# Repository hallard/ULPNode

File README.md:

ULPNode
=======

Utra Low Power Wireless Arduino Node

For some time being, I researching a way to have to have a kind of “universal” Arduino node sensor.  
When I say universal, I’m talking about connecting to it several sensors like Temperature, Humidity, Lux,… such as LDR, NTC, PTC, DHT11, DHT22, DS18B20, I2C sensors.  

At 1st research I tried lot existing, they  works fine, but as soon as you want to power them with classic battery (one AAA, CR2032, …) you’re facing other challenges, be able to maximize the battery life and also be able to send wireless frames until battery is reaching it’s end of life.

##Blog dedicated post
See this [post][2] for detailed and technical information

##License

Copyright Charles-Henri Hallard (2014)  
[Attribution-ShareAlike CC BY-SA][6]

##Misc
Do not hesitate to look on news and other projects on my [blog][1] 
 
[1]: http://hallard.me
[2]: http://hallard.me/bp-ulpnode/
[3]: http://hallard.me/ulpnode-bootloader/
[6]: https://creativecommons.org/licenses/

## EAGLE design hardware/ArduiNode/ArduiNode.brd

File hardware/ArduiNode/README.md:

Arduinode V1.3
==============

Very first early prototype of Utra Low Power Wireless Arduino Node. In fact it's amazing how often I use this board for testing, it runs on 3.3V, has RFM12B RFM69 connector, NRF24 style connector, I2C Oled connector and some sensors connectors.

It does not include the [Low Power][5] engine of ULPNode but it's a really cool testing board.

**This is not the final design**, this board was done to implement 1st testing and POC, it's posted there as reference only and as help on some Arduino Sketch I wrote that I use with this board. It also include 2 little battery power testing board with different version of MCP1640 DC/DC booster.

##Blog dedicated categories
See this [post][4] for detailed and technical information on ULPNode

##License

Copyright Charles-Henri Hallard (2014)  
[Attribution-ShareAlike CC BY-SA][6]

##Misc
Do not hesitate to look on news and other projects on my [blog][1] 

##schematics

Do not hesitate to look on news and other projects on my [blog][1] 
 
[1]: http://hallard.me
[2]: http://hallard.me/bp-ulpnode/
[3]: http://hallard.me/ulpnode-bootloader/
[4]: http://hallard.me/category/ulpnode/
[5]: http://hallard.me/ulpnode-low-power-secret/
[6]: https://creativecommons.org/licenses/

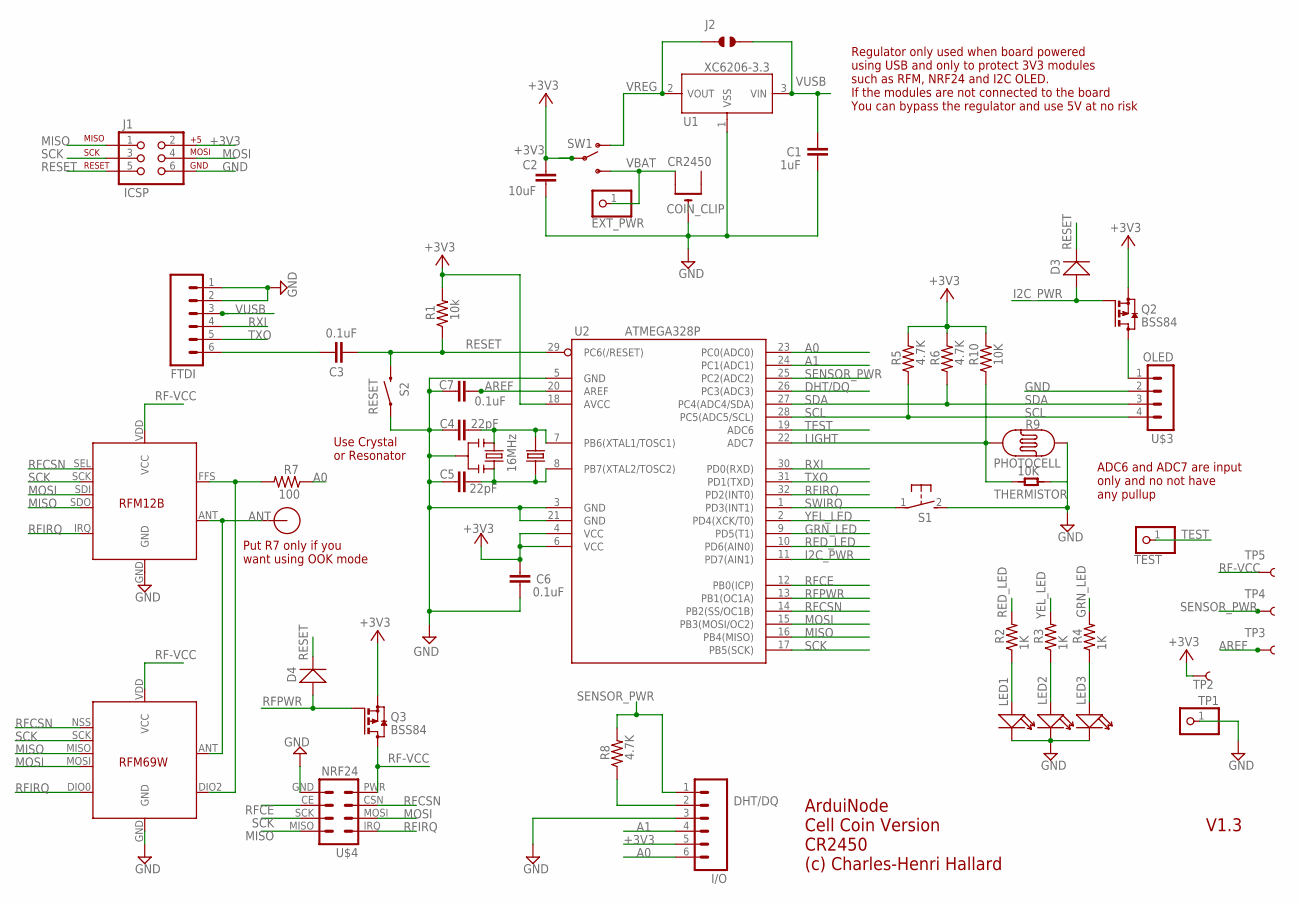
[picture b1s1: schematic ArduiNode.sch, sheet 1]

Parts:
C1: 1uF; C0805K
C2: 10uF; C0805K
C3, C6, C7: 0.1uF; C0805K
C4, C5: 22pF; C0805K
COIN_CLIP: CR2450; CR1220-THM
D3, D4: D-SOD-123; SOD123
EXT_PWR: PINHD-1X1CB; 1X01-CLEANBIG
FTDI: M06SIP_LOCK; 1X06-SIP_LOCK
I/O: M06FEMALE_LOCK; 1X06_FEMALE_LOCK.010
J1: ICSP; 2X3_LOCK
J2: JUMPER_SOLDER_1X2
LED1, LED2, LED3: LED0805; LED-0805
Q2, Q3: BSS84; SOT23
R1: 10k; M0805
R2, R3, R4: 1K; M0805
R5, R6, R8: 4.7K; M0805
R7: 100; M0805
R9: PHOTOCELL
R10: 10K; M0805
RFM12B: RFM12BNO; RFM12B
S1: DTS-3
S2: RESET; TACTILE-SWITCH-1101NE
SW1: USB_COIN; SWITCH-SPDT-SMD
TEST: PINHD-1X1CB; 1X01-CLEANBIG
THERMISTOR: 10K; R0603
TP1: PINHD-1X1; 1X01
TP2, TP3, TP4, TP5: TEST-POINT3X5; PAD.03X.05
U1: XC6206-3.3; SOT23
U2: ATMEGA328P; TQFP32
U$3: OLED; 1X04_LOCK
U$4: NRF24; 2X04_LOCK
U$11: RFM12B_ANTENNA; RFM12B-ANTENNA
X2: 16MHz; 2P-SMD-5.0X3.2
X3: RFM69; RFM69W-MINPADS
Y1: 16MHz; RESONATOR-SMD

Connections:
+3V3: C2.1, C6.2, I/O.5, J1.2, Q2.2 (S), Q3.2 (S), R1.2, R5.2, R6.2, R10.2, SW1.2, TP2.P$1, U2.4 (VCC), U2.6 (VCC), U2.18 (AVCC)
A0: I/O.6, R7.1, U2.23 (PC0(ADC0))
A1: I/O.4, U2.24 (PC1(ADC1))
ANT: RFM12B.ANT, U$11.P$1, X3.ANT
AREF: C7.1, TP3.P$1, U2.20 (AREF)
DHT/DQ: I/O.2, R8.1, U2.26 (PC3(ADC3))
DTR: C3.1, FTDI.6
GND: C1.2, C2.2, C4.2, C5.2, C6.1, C7.2, COIN_CLIP.GND (-), FTDI.1, FTDI.2, I/O.3, J1.6, LED1.-, LED2.-, LED3.-, R9.1, RFM12B.GND, S1.2, S2.P$1 (1), THERMISTOR.1, TP1.1, U1.1 (VSS), U2.3 (GND), U2.5 (GND), U2.21 (GND), U$3.2, U$4.GND, X3.GND, Y1.2
GRN_LED: R4.2, U2.9 (PD5(T1))
I2C_PWR: D3.+, Q2.1 (G), U2.11 (PD7(AIN1))
LIGHT: R9.2, R10.1, THERMISTOR.2, U2.22 (ADC7)
MISO: J1.1, RFM12B.SDO, U2.16 (PB4(MISO)), U$4.MISO, X3.MISO
MOSI: J1.4, RFM12B.SDI, U2.15 (PB3(MOSI/OC2)), U$4.MOSI, X3.MOSI
unnamed: R7.2, RFM12B.FFS, X3.DIO2
unnamed: LED1.+, R2.1
unnamed: LED2.+, R3.1
unnamed: LED3.+, R4.1
unnamed: Q2.3 (D), U$3.1
RED_LED: R2.2, U2.10 (PD6(AIN0))
RESET: C3.2, D3.-, D4.-, J1.5, R1.1, S2.P$2 (2), U2.29 (PC6(/RESET))
RF-VCC: Q3.3 (D), RFM12B.VDD (VCC), TP5.P$1, U$4.PWR (VCC), X3.VDD (VCC)
RFCE: U2.12 (PB0(ICP)), U$4.CE
RFCSN: RFM12B.SEL, U2.14 (PB2(SS/OC1B)), U$4.CSN, X3.NSS (SEL)
RFIRQ: RFM12B.IRQ, U2.32 (PD2(INT0)), U$4.IRQ, X3.DIO0
RFPWR: D4.+, Q3.1 (G), U2.13 (PB1(OC1A))
RXI: FTDI.4, U2.30 (PD0(RXD))
SCK: J1.3, RFM12B.SCK, U2.17 (PB5(SCK)), U$4.SCK (CLK), X3.SCK
SCL: R5.1, U2.28 (PC5(ADC5/SCL)), U$3.4
SDA: R6.1, U2.27 (PC4(ADC4/SDA)), U$3.3
SENSOR_PWR: I/O.1, R8.2, TP4.P$1, U2.25 (PC2(ADC2))
SWIRQ: S1.1, U2.1 (PD3(INT1))
TEST: TEST.1, U2.19 (ADC6)
TXO: FTDI.5, U2.31 (PD1(TXD))
VBAT: COIN_CLIP.+1 (+), EXT_PWR.1, SW1.1
VREG: J2.1, SW1.3, U1.2 (VOUT)
VUSB: C1.1, FTDI.3, J2.2, U1.3 (VIN)
X1: C5.1, U2.8 (PB7(XTAL2/TOSC2)), X2.1, Y1.3
XTAL1: C4.1, U2.7 (PB6(XTAL1/TOSC1)), X2.2, Y1.1
YEL_LED: R3.2, U2.2 (PD4(XCK/T0))

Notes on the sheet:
V1.3
ArduiNode Cell Coin Version CR2450 (c) Charles-Henri Hallard
Put R7 only if you want using OOK mode
Regulator only used when board powered using USB and only to protect 3V3 modules such as RFM, NRF24 and I2C OLED. If the modules are not connected to the board You can bypass the regulator and use 5V at no risk
ADC6 and ADC7 are input only and no not have any pullup
Use Crystal or Resonator

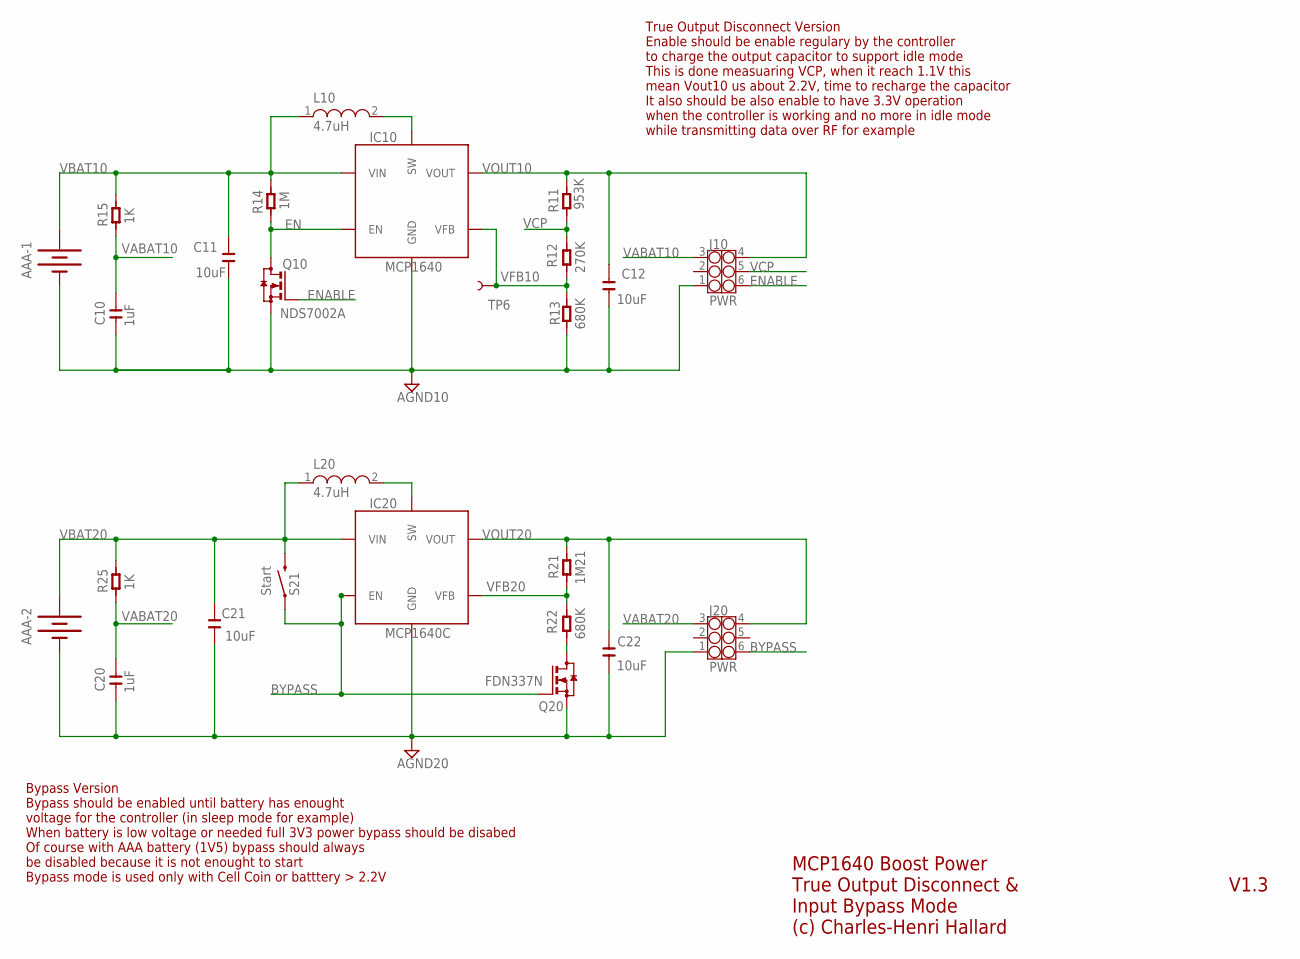
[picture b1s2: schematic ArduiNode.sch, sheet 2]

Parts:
AAA-1, AAA-2: BATTERYAAA-JL; BATTERY-AAA-JL
C10, C20: 1uF; C0805
C11, C12, C21, C22: 10uF; C0805
IC10: MCP1640; SOT23-6
IC20: MCP1640C; SOT23-6
J10, J20: PWR; 2X3P-2.54-2.54-11.6-3.0-BLACK-MALE
L10, L20: 4.7uH; L1812
Q10: NDS7002A; SOT23
Q20: FDN337N; SOT23
R11: 953K; R0603
R12: 270K; R0603
R13, R22: 680K; R0603
R14: 1M; R0603
R15, R25: 1K; R0603
R21: 1M21; R0603
S21: Start; TACTILE-SWITCH-1101NE
TP6: TEST-POINT3; PAD.03X.03

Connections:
AGND10: AAA-1.GND@1 (-), C10.1, C11.1, C12.1, IC10.2 (GND), J10.1, Q10.2 (S), R13.1
AGND20: AAA-2.GND@1 (-), C20.1, C21.1, C22.1, IC20.2 (GND), J20.1, Q20.2 (S)
BYPASS: IC20.3 (EN), J20.6, Q20.1 (G), S21.P$1 (1)
EN: IC10.3 (EN), Q10.3 (D), R14.1
ENABLE: J10.6, Q10.1 (G)
unnamed: Q20.3 (D), R22.1
SW: IC10.1 (SW), L10.2
SW20: IC20.1 (SW), L20.2
VABAT10: C10.2, J10.3, R15.1
VABAT20: C20.2, J20.3, R25.1
VBAT10: AAA-1.PWR@1 (+), C11.2, IC10.6 (VIN), L10.1, R14.2, R15.2
VBAT20: AAA-2.PWR@1 (+), C21.2, IC20.6 (VIN), L20.1, R25.2, S21.P$2 (2)
VCP: J10.5, R11.1, R12.2
VFB10: IC10.4 (VFB), R12.1, R13.2, TP6.P$1
VFB20: IC20.4 (VFB), R21.1, R22.2
VOUT10: C12.2, IC10.5 (VOUT), J10.4, R11.2
VOUT20: C22.2, IC20.5 (VOUT), J20.4, R21.2

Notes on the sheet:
MCP1640 Boost Power True Output Disconnect & Input Bypass Mode (c) Charles-Henri Hallard
True Output Disconnect Version Enable should be enable regulary by the controller to charge the output capacitor to support idle mode This is done measuaring VCP, when it reach 1.1V this mean Vout10 us about 2.2V, time to recharge the capacitor It also should be also enable to have 3.3V operation w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
Bypass Version Bypass should be enabled until battery has enought voltage for the controller (in sleep mode for example) When battery is low voltage or needed full 3V3 power bypass should be disabed Of course with AAA battery (1V5) bypass should always be disabled because it is not enought to start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
V1.3

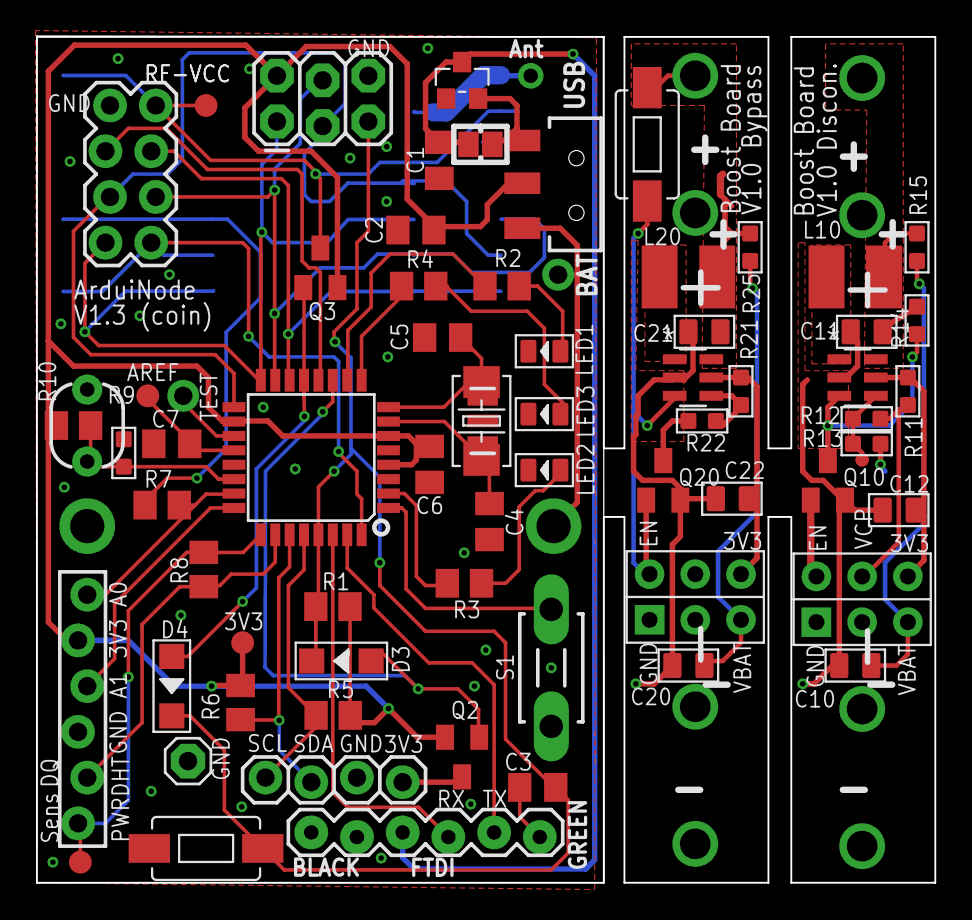
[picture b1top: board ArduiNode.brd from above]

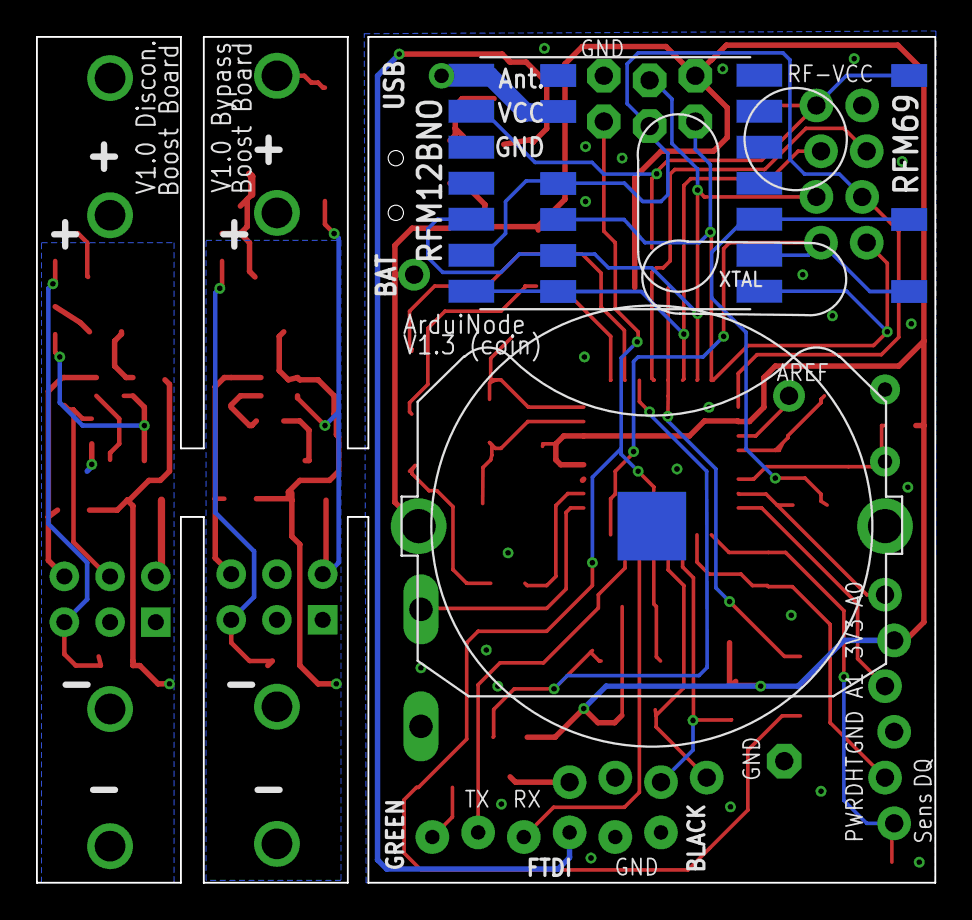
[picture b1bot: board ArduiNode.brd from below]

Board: 2 copper layers, 49.9 x 47.0 mm, 75 parts (3 on the bottom side), 56 nets.

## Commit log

2014-09-21 :confetti_ball: Added .gitattributes & .gitignore files
2014-09-21 Original Optiboot V6.2
    Cloned from google code trunk
2014-09-21 Presentation
2014-09-24 Modified for ULPNode
    First commit, modified for ULPNode, added sample sketch to call
    bootloader function
2014-09-24 Installation path typo error
2014-09-24 Added some comments
2014-09-24 Changed look & feel
2015-01-14 Updated speed to 8MHz
    Changed running speed to 8MHz instead of 4MHz to avoid WS2812B driving
    problem
2015-01-14 Creation
    The compiled ULPNode HEX file
2015-06-15 Moved Repo link
2015-06-15 File deleted repo moved
2015-07-14 Creation
    published as reference only
2015-07-14 Added schematics image

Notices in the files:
parts and their libraries:
SparkFun-Sensors: Licensing: CC v3.0 Share-Alike You are welcome to use this library for commercial purposes.
